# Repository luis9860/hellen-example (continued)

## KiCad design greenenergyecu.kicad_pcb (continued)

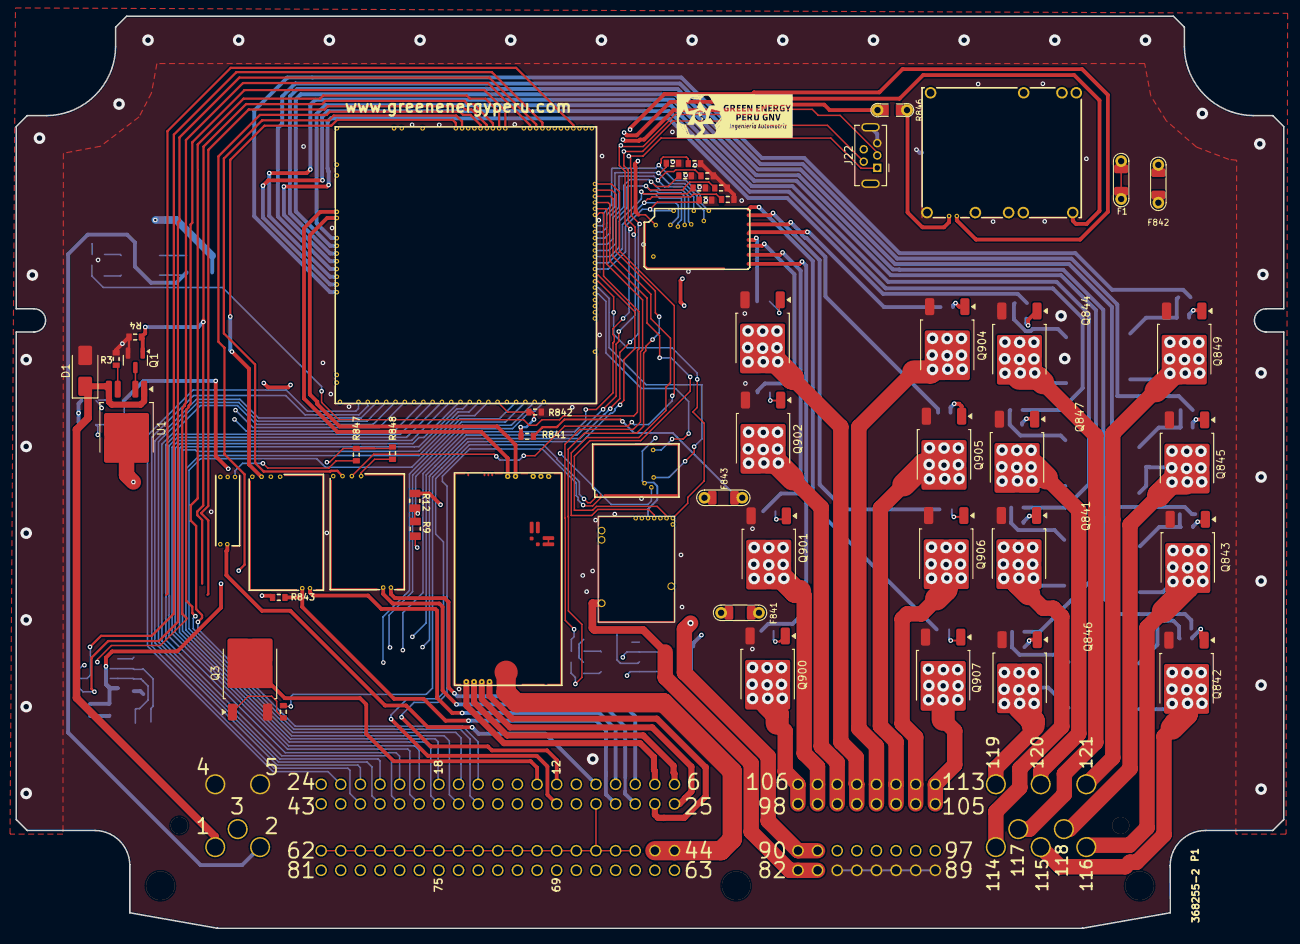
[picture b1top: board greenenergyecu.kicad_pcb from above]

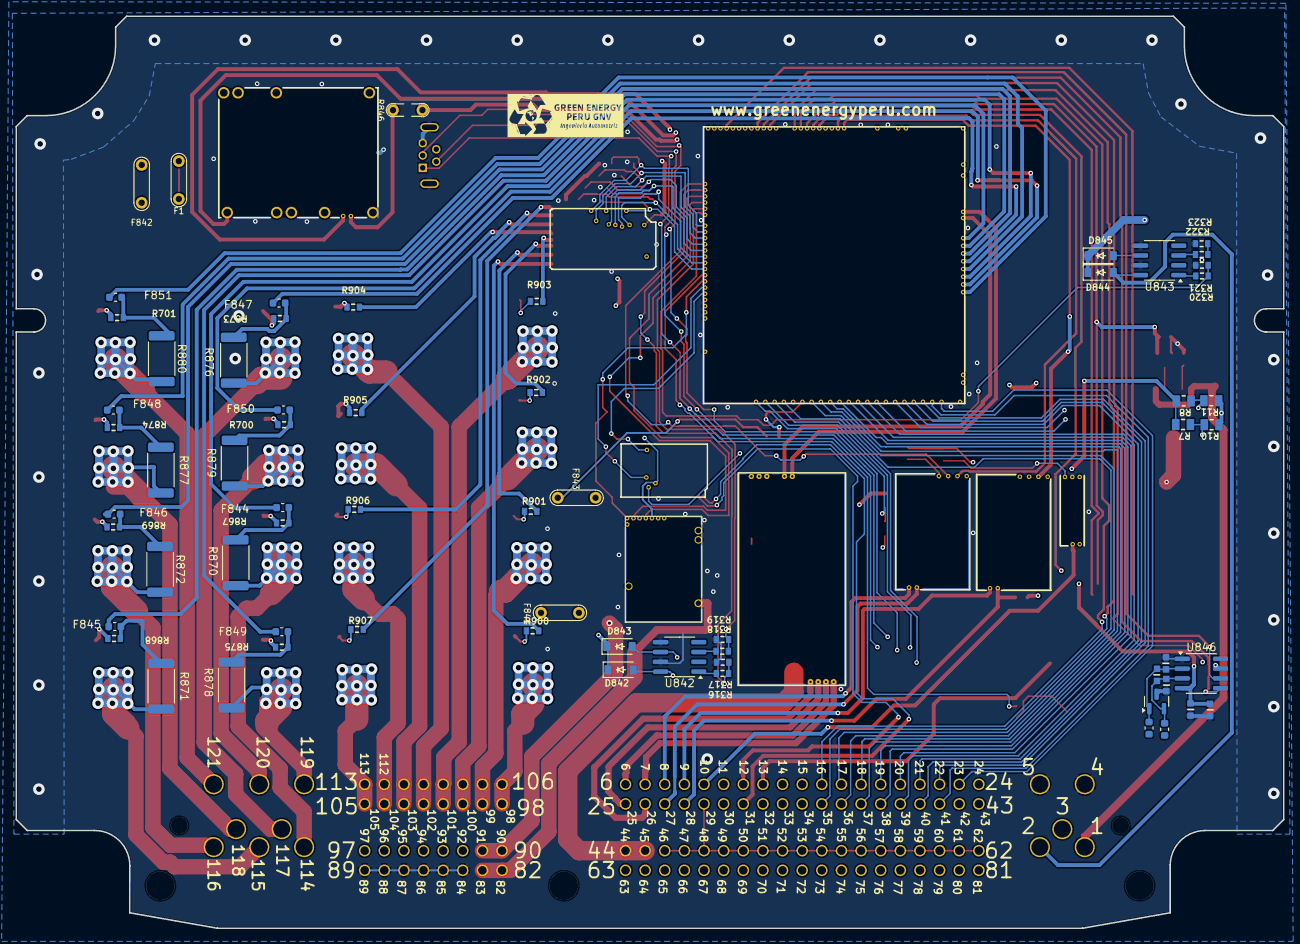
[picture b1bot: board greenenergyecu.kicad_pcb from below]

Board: 4 copper layers, 164.0 x 118.0 mm, 113 parts (59 on the bottom side), 159 nets.

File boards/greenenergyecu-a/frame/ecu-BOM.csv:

Comment,Designator,Footprint,LCSC Part #
"100n","C4","C0603","C14663"
"1u","C5","C0603","C15849"
"10n","C843","C0603","C57112"
"10n","C844","C0603","C57112"
"100n","C845","C0603","C14663"
"SS34","D1","D_SMA","C5119706"
"B5819W","D842","SOD-123","C8598"
"B5819W","D843","SOD-123","C8598"
"B5819W","D844","SOD-123","C8598"
"B5819W","D845","SOD-123","C8598"
"NUP2105L","D846","SOT-23","C284104"
"12H1500D","F1","PAD-1206-PAD","C182446"
"12H1500D","F841","PAD-1206-PAD","C182446"
"12H1500D","F842","PAD-1206-PAD","C182446"
"12H1500D","F843","PAD-1206-PAD","C182446"
"50mA","F844","Fuse_0603_1608Metric","C369141"
"50mA","F845","Fuse_0603_1608Metric","C369141"
"50mA","F846","Fuse_0603_1608Metric","C369141"
"50mA","F847","Fuse_0603_1608Metric","C369141"
"50mA","F848","Fuse_0603_1608Metric","C369141"
"50mA","F849","Fuse_0603_1608Metric","C369141"
"50mA","F850","Fuse_0603_1608Metric","C369141"
"50mA","F851","Fuse_0603_1608Metric","C369141"
"USB_B_Mini","J22","USB-MINI-B-VERTICAL","C2682228"
"470R@100MHz","L841","L_0603_1608Metric","C97853"
"470R@100MHz","L842","L_0603_1608Metric","C97853"
"Module:power_12and5V/0.3","M1","power_12and5V",""
"Module:knock/0.2","M2","knock",""
"Module:vr-discrete/0.5","M3","vr-discrete",""
"Module:vr-max9924/0.1","M4","vr-max9924",""
"Module:wbo/0.5","M5","wbo",""
"Module:mega-mcu100/0.3","M6","mega-mcu100",""
"Module:can/0.1","M7","can",""
"Module:motor-driver/0.1","M8","motor-driver",""
"Module:ign8/0.2","M9","ign8",""
"368255-2","P1","368255-2","C392284"
"AO3400A","Q1","SOT-23","C20917"
"ISL9V3040D3ST","Q3","DPAK","C903784"
"ISL9V3040D3ST","Q841","DPAK","C462128"
"ISL9V3040D3ST","Q842","MODIGBT","C462128"
"ISL9V3040D3ST","Q843","MODIGBT","C462128"
"ISL9V3040D3ST","Q844","DPAK","C462128"
"ISL9V3040D3ST","Q845","MODIGBT","C462128"
"ISL9V3040D3ST","Q846","DPAK","C462128"
"ISL9V3040D3ST","Q847","DPAK","C462128"
"ISL9V3040D3ST","Q849","MODIGBT","C462128"
"ISL9V3040D3ST","Q900","DPAK","C5350881"
"ISL9V3040D3ST","Q901","abel-252-2","C5350881"
"ISL9V3040D3ST","Q902","DPAK","C5350881"
"ISL9V3040D3ST","Q903","DPAK","C5350881"
"ISL9V3040D3ST","Q904","DPAK","C5350881"
"ISL9V3040D3ST","Q905","DPAK","C5350881"
"ISL9V3040D3ST","Q906","DPAK","C5350881"
"ISL9V3040D3ST","Q907","DPAK","C5350881"
"22","R1","R0603","C23345"
"1k","R3","R0603","C21190"
"4.7k","R4","R0603","C23162"
"DNP","R7","R0805",""
"DNP","R8","R0805",""
"DNP","R9","R0805",""
"10k","R10","R0805","C17414"
"10k","R11","R0805","C17414"
"10k","R12","R0805","C17414"
"10k","R305","R0603","C17414"
"10k","R307","R0603","C17414"
"10k","R309","R0603","C17414"
"10k","R311","R0603","C17414"
"10k","R313","R0603","C17414"
"10k","R315","R0603","C17414"
"4.7k","R316","R0603","C23162"
"4.7k","R317","R0603","C23162"
"4.7k","R318","R0603","C23162"
"4.7k","R319","R0603","C23162"
"4.7k","R320","R0603","C23162"
"4.7k","R321","R0603","C23162"
"4.7k","R322","R0603","C23162"
"4.7k","R323","R0603","C23162"
"10k","R325","R0603","C17414"
"10k","R327","R0603","C17414"
"22","R700","R0603","C23345"
"22","R701","R0603","C23345"
"33k","R841","R0603","C4216"
"6.8k","R842","R0603","C23212"
"4.7k","R843","R0603",""
"Jumper-Pad-Pad","R846","PAD-0805-PAD","C17477"
"0","R847","R0603","C21189"
"0","R848","R0603",""
"22","R867","R0603","C23345"
"22","R868","R0603","C23345"
"22","R869","R0603","C23345"
"0","R870","R2512",""
"0","R871","R2512",""
"0","R872","R2512",""
"22","R873","R0603","C23345"
"22","R874","R0603","C23345"
"22","R875","R0603","C23345"
"0","R876","R2512",""
"0","R877","R2512",""
"0","R878","R2512",""
"0","R879","R2512",""
"0","R880","R2512",""
"22","R900","R0603","C23345"
"22","R901","R0603","C23345"
"22","R902","R0603","C23345"
"22","R903","R0603","C23345"
"22","R904","R0603","C23345"
"22","R905","R0603","C23345"
"22","R906","R0603","C23345"
"22","R907","R0603","C23345"
"BTS6143D","U1","TO-252-4","C95232"
"VNLD5160TR-E","U842","SO8","C377942"
"VNLD5160TR-E","U843","SO8","C377942"
"MAX31855KASA","U846","SO8","C52028"

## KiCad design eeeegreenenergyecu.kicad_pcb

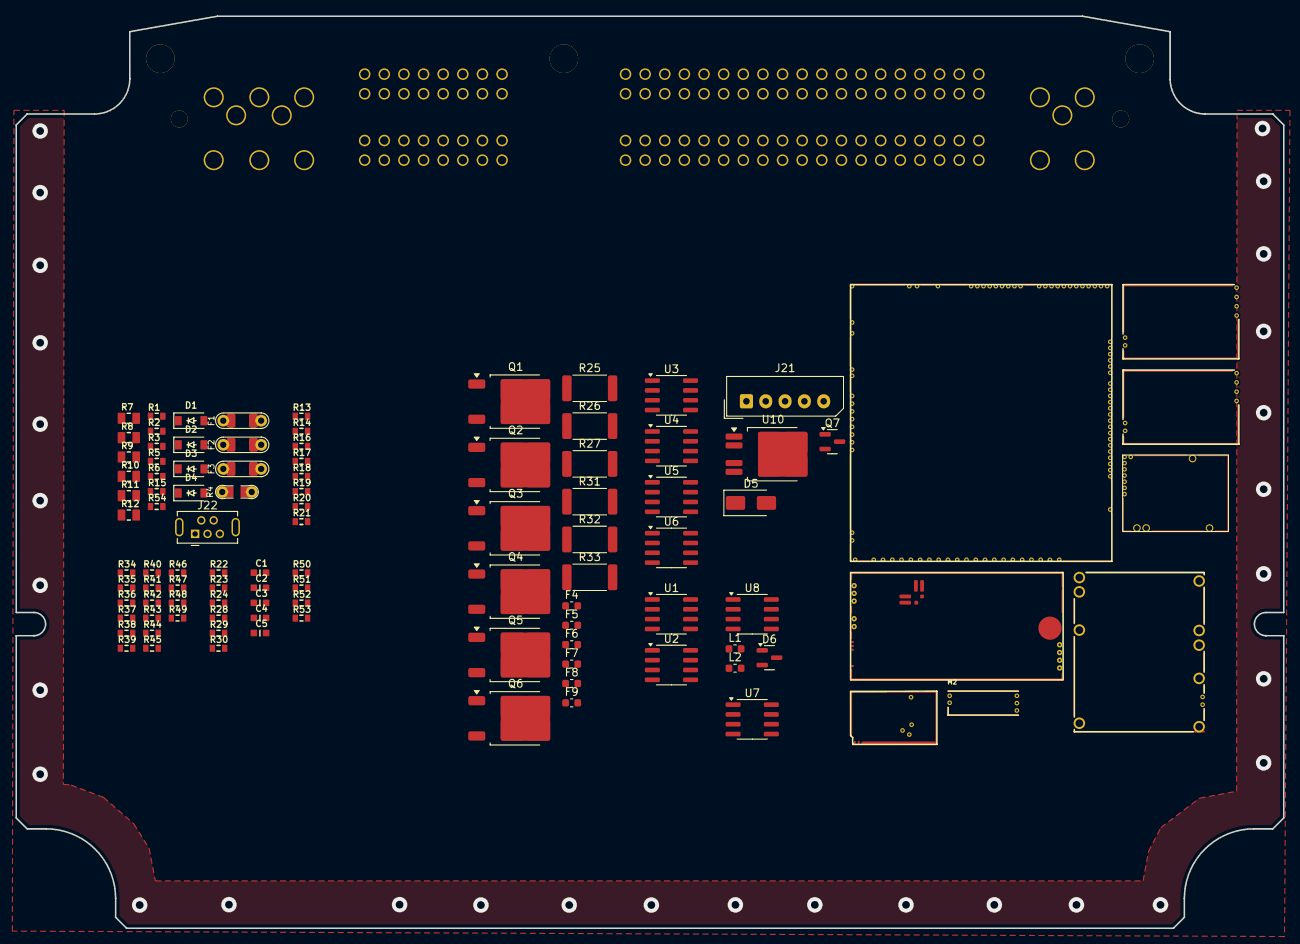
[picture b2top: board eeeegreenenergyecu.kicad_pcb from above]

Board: 4 copper layers, 164.0 x 118.0 mm, 103 parts (0 on the bottom side), 142 nets, no tracks yet.

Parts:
C1, C3: 10n; C0603
C2, C4: 100n; C0603
C5: 1u; C0603
D1, D2, D3, D4: B5819W; SOD-123
D5: SS34; D_SMA
D6: NUP2105L; SOT-23
F1, F2, F3: 12H1500D; PAD-1206-PAD
F4, F5, F6, F7, F8, F9: 50mA; Fuse_0603_1608Metric
J21: Conn_01x05_Male; Molex_SPOX_5267-05A_1x05_P2.50mm_Vertical
J22: USB_B_Mini; USB-MINI-B-VERTICAL
L1, L2: 470R@100MHz; L_0603_1608Metric
M1: Module-power_12and5V-0.3; power_12and5V
M2: Module-knock-0.2; knock
M3: Module-vr-discrete-0.5; vr-discrete
M4: Module-vr-max9924-0.1; vr-max9924
M5: Module-wbo-0.5; wbo
M6: Module:mega-mcu100/0.3; mega-mcu100
M7: Module-can-0.1; can
M8: Module-motor-driver-0.1; motor-driver
P1: 368255-2
Q1, Q2, Q3, Q4, Q5, Q6: ISL9V3040D3ST; TO-252-2
Q7: AO3400A; SOT-23
R1, R13, R14, R15, R16, R17, R18, R19, R20, R21, R34, R35, R36, R37, R38, R39, R40, R41, R42, R43, R44, R45, R46, R47, R48, R49, R50, R51, R52, R53: 4.7k; R0603
R2: 33k; R0603
R3: 6.8k; R0603
R4: Jumper-Pad-Pad; PAD-0805-PAD
R5, R6: 0; R0603
R7, R8, R9: DNP; R0805
R10, R11, R12: 10k; R0805
R22, R23, R24, R28, R29, R30: 22; R0603
R25, R26, R27, R31, R32, R33: 0; R_2512_6332Metric
R54: 1k; R0603
U1, U2, U3, U4, U5, U6, U7: VNLD5160TR-E; SOIC-8_3.9x4.9mm_P1.27mm
U8: MAX31855KASA; SOIC-8_3.9x4.9mm_P1.27mm
U10: BTS6143D; TO-252-4

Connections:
+3.3V: M6.N21 (V33), M8.W5 (3V3_IN)
+3.3VA: C4.2, C5.2, M6.N15 (V33_SWITCHABLE), M7.V2 (CAN_VIO), U8.4 (V_CC)
+5V: M1.E4 (V5), M6.N22 (VCC)
+5VA: M2.E1 (V5A), M3.E4 (V5_IN), M4.E4 (V5_IN), M5.W1 (V5_IN), M6.E1 (V5A_SWITCHABLE), M6.W2 (V5A_SWITCHABLE), M7.V1 (V5), R7.2, R8.2, R9.2
/ADC3: M6.S15 (IN_KNOCK_(PA2)), R5.2, R6.2
/DC1_DIR: M6.E21 (OUT_PWM4_(PC8)), M8.W4 (DIR)
/DC1_PWM: M6.E20 (OUT_PWM3_(PC7)), M8.W2 (PWM)
/EGT/SPI_CS: M6.N9 (SPI3_CS_(PA15)), U8.6 (~CS)
/IGN1: F4.2, M6.W10 (IGN1_(PC13))
/IGN2: F5.2, M6.W9 (IGN2_(PE5))
/IGN3: F6.2, M6.W8 (IGN3_(PE4))
/IGN4: F7.2, M6.W7 (IGN4_(PE3))
/IGN5: F8.2, M6.W6 (IGN5_(PE2))
/IGN6: F9.2, M6.W5 (IGN6_(PB8))
/INJ1: M6.E17 (OUT_INJ1_(PD3)), R38.1, R39.1
/INJ2: M6.E16 (OUT_INJ2_(PA9)), R40.1, R41.1
/INJ3: M6.E15 (OUT_INJ3_(PD11)), R42.1, R43.1
/INJ4: M6.E14 (OUT_INJ4_(PD10)), R44.1, R45.1
/INJ5: M6.E13 (OUT_INJ5_(PD2)), R46.1, R47.1
/INJ6: M6.E12 (OUT_INJ6_(PA8)), R48.1, R49.1
/IN_KNOCK: M2.E3 (OUT_KNOCK), R5.1
/IN_VIGN: F1.2, M1.V2 (IN_VIGN)
/IN_VMAIN: M6.S6 (IN_AUX4_(PC5)), R2.1, R3.2
/LS1: M6.E11 (OUT_INJ7_(PD15)), R13.1, R16.1
/LS2: M6.E10 (OUT_INJ8_(PD12)), R14.1, R17.1
/LS3: M6.E18 (OUT_PWM1_(PD13)), R18.1, R20.1
/LS4: M6.E19 (OUT_PWM2_(PC6)), R19.1, R21.1
/LS_HOT1: M6.W4 (IGN7_(PB9)), R52.1, R53.1
/LS_HOT2: M6.W3 (IGN8_(PE6)), R50.1, R51.1
/MISO3: M6.N11 (SPI3_MISO_(PC11)), U8.7 (SO)
/PG_5VP: M6.N12 (SPI3_MOSI_(PC12)), R4.2
/PWR_EN: M1.E5 (EN_5VP), M6.N20 (OUT_PWR_EN_(PE10))
/SCK3: M6.N10 (SPI3_SCK_(PC10)), U8.5 (SCK)
/USB+: J21.3, J22.3 (D+), M6.N3 (USBP_(PA12))
/USB-: J21.2, J22.2 (D-), M6.N2 (USBM_(PA11))
/VBAT: M1.E1 (VBAT), M6.N17 (VBAT)
/VBUS: J21.1, J22.1 (VBUS), M6.N1 (VBUS)
/VIGN: M1.E3 (VIGN), M6.E5 (IN_VIGN_(PA5))
/VREF1: M2.W2 (VREF), M6.S22 (VREF1)
/VR_DISCRETE: M3.E3 (OUT), M6.N18 (UART8_RX_(PE0))
/VR_DISCRETE_A: M3.E2 (OUT_A), R6.1
/VR_DISCRETE_THR: M3.E1 (Thresh_IN), M6.E23 (OUT_PWM6_(PD14))
/VR_MAX9924: M4.E3 (OUT), M6.N19 (UART8_TX_(PE1))
DC1_DIS_W1: M6.E8 (SPI2_MISO_(PB14)), M8.W1 (DIS)
E6INJ7CANRX: M6.E6 (SPI2_CS_/_CAN2_RX_(PB12)), M7.V6 (CAN_RX), R34.1, R37.1
E7INJ8CANTX: M6.E7 (SPI2_SCK_/_CAN2_TX_(PB13)), M7.V5 (CAN_TX), R35.1, R36.1
unnamed: F3.2, M8.N2 (12V_IN), M8.S1 (12V_IN)
unnamed: F4.1, R22.2, R25.1
unnamed: F5.1, R23.2, R26.1
unnamed: F6.1, R24.2, R27.1
unnamed: F7.1, R28.2, R31.1
unnamed: F8.1, R29.2, R32.1
unnamed: F9.1, R30.2, R33.1
unnamed: M1.E6 (PG_5VP), R4.1
unnamed: M5.J1 (SEL1), M5.J_GND1 (PULL_DOWN1)
unnamed: M6.N14a (LED_GREEN), Q7.1 (G), R15.1
unnamed: Q1.1 (G), R22.1
unnamed: Q2.1 (G), R23.1
unnamed: Q3.1 (G), R24.1
unnamed: Q4.1 (G), R28.1
unnamed: Q5.1 (G), R29.1
unnamed: Q6.1 (G), R30.1
unnamed: Q7.3 (D), U10.2 (IN)
unnamed: R13.2, U1.1 (IN1)
unnamed: R14.2, U1.3 (IN2)
unnamed: R18.2, U2.1 (IN1)
unnamed: R19.2, U2.3 (IN2)
unnamed: R34.2, U3.1 (IN1)
unnamed: R36.2, U3.3 (IN2)
unnamed: R42.2, U4.1 (IN1)
unnamed: R45.2, U4.3 (IN2)
unnamed: R46.2, U5.1 (IN1)
unnamed: R48.2, U5.3 (IN2)
unnamed: R38.2, U6.1 (IN1)
unnamed: R41.2, U6.3 (IN2)
unnamed: R50.2, U7.1 (IN1)
unnamed: R52.2, U7.3 (IN2)
unnamed: C2.2, C3.2, D6.2 (K), L1.2, U8.3 (T+)
unnamed: C1.2, C2.1, D6.1 (K), L2.2, U8.2 (T-)
unnamed: R54.1, U10.4 (IS)
PIN1: M8.S3 (OUT+), P1.1
PIN2: M8.S2 (OUT-), P1.2
PIN6: M6.N14 (UART2_RX_(PD6)), P1.6
PIN7: M6.N13 (UART2_TX_(PD5)), P1.7
PIN8: P1.8, Q6.2 (C), R33.2
PIN9: P1.9, Q4.2 (C), R31.2
PIN10: P1.10, Q3.2 (C), R27.2
PIN11: P1.11, Q5.2 (C), R32.2
PIN12: P1.12, Q2.2 (C), R26.2
PIN13: P1.13, Q1.2 (C), R25.2
PIN14: D1.2 (A), P1.14, U1.8 (D1)
PIN15: D2.2 (A), P1.15, U1.6 (D2)
PIN16: D3.2 (A), P1.16, U2.8 (D1)
PIN17: M3.W2 (VR+), P1.17
PIN18: M3.W1 (VR-), P1.18
PIN19: M4.W2 (VR+), P1.19
PIN20: M4.W1 (VR-), P1.20, R1.2
PIN21: L1.1, P1.21
PIN22: L2.1, P1.22
PIN34: M6.S2 (IN_D3_(PE14)), P1.34
PIN35: M6.S3 (IN_D2_(PE13)), P1.35
PIN36: M6.S4 (IN_D1_(PE12)), P1.36
PIN37: M6.S13 (IN_MAP1_(PC0)), P1.37
PIN38: M6.S18 (IN_TPS_(PA4)), P1.38
PIN39: M6.S9 (IN_AUX1_(PB0)), P1.39
PIN40: M6.S11 (IN_O2S_/_CAN_WAKEUP_(PA0)), P1.40
PIN41: M6.S10 (IN_O2S2_(PA1)), P1.41
PIN42: M6.S17 (IN_VSS_(PE11)), P1.42
PIN43: D5.1 (K), P1.43, U10.1 (OUT), U10.5 (OUT)
PIN44: P1.44, U6.8 (D1)
PIN45: P1.45, U6.6 (D2)
PIN46: P1.46, U4.8 (D1)
PIN47: P1.47, U4.6 (D2)
PIN48: P1.48, U5.8 (D1)
PIN49: P1.49, U5.6 (D2)
PIN50: P1.50, U3.8 (D1)
PIN51: P1.51, U3.6 (D2)
PIN63: M6.S20 (IN_IAT_(PC3)), P1.63
PIN65: M6.S21 (IN_CLT_(PC2)), P1.65
PIN81: M2.W1 (IN_KNOCK), P1.81
PIN82: M5.W4 (CANH), M6.W11 (CANH), P1.82
PIN83: M5.W3 (CANL), M6.W12 (CANL), P1.83
PIN84: M6.S14 (IN_CRANK_(PB1)), P1.84, R7.1, R10.2
PIN85: M6.S16 (IN_CAM_(PA6)), P1.85, R8.1, R11.2
PIN86: P1.86, U7.6 (D2)
PIN87: P1.87, U7.8 (D1)
PIN88: D4.2 (A), P1.88, U2.6 (D2)
PIN89: M6.S1 (IN_D4_(PE15)), P1.89, R9.1, R12.2
PIN90: M6.S19 (IN_PPS_(PA3)), P1.90
PIN91: M6.S8 (IN_AUX2_(PC4/PE9)), P1.91
PIN102: M5.E4 (LSU_Rtrim), P1.102
PIN103: M5.E3 (LSU_Ip), P1.103
PIN104: M5.E2 (LSU_Vm), P1.104
PIN105: M5.E1 (LSU_Un), P1.105
PIN106: M1.V4 (5VP), P1.71, P1.72, P1.73, P1.74, P1.75, P1.76, P1.77, P1.78, P1.79, P1.80, P1.106, P1.107, R1.1
PIN108: F1.1, P1.108
PIN113: M6.W1 (GNDA), P1.52, P1.53, P1.54, P1.55, P1.56, P1.57, P1.58, P1.59, P1.60, P1.61, P1.62, P1.64, P1.66, P1.68, P1.98, P1.99, P1.113, R10.1, R11.1, R12.1
PIN114: C1.1, C3.1, C4.1, C5.1, D5.2 (A), D6.3 (A), J21.4, J21.5, J22.5 (GND), J22.6 (Shield), M1.S1 (GND), M2.E2 (GND), M3.G (GND), M4.G (GND), M5.E6 (LSU_H-), M5.G (GND), M6.G (GND), M7.E1 (GND), M8.G (GND), P1.3, P1.114, P1.115, Q1.3 (E), Q2.3 (E), Q3.3 (E), Q4.3 (E), Q5.3 (E), Q6.3 (E), Q7.2 (S), R3.1, R15.2, R16.2, R17.2, R20.2, R21.2, R35.2, R37.2, R39.2, R40.2, R43.2, R44.2, R47.2, R49.2, R51.2, R53.2, R54.2, U1.5 (S2), U1.7 (S1), U2.5 (S2), U2.7 (S1), U3.5 (S2), U3.7 (S1), U4.5 (S2), U4.7 (S1), U5.5 (S2), U5.7 (S1), U6.5 (S2), U6.7 (S1), U7.5 (S2), U7.7 (S1), U8.1 (GND)
PIN116: M1.V1 (V12_PERM), P1.116
PIN117: D1.1 (K), D2.1 (K), D3.1 (K), D4.1 (K), F2.2, M1.V3 (V12_RAW), P1.117
PIN119: M5.E5 (LSU_H+), P1.119
PIN120: F2.1, F3.1, P1.23, P1.24, P1.120, R2.2, U10.3 (Vbb)

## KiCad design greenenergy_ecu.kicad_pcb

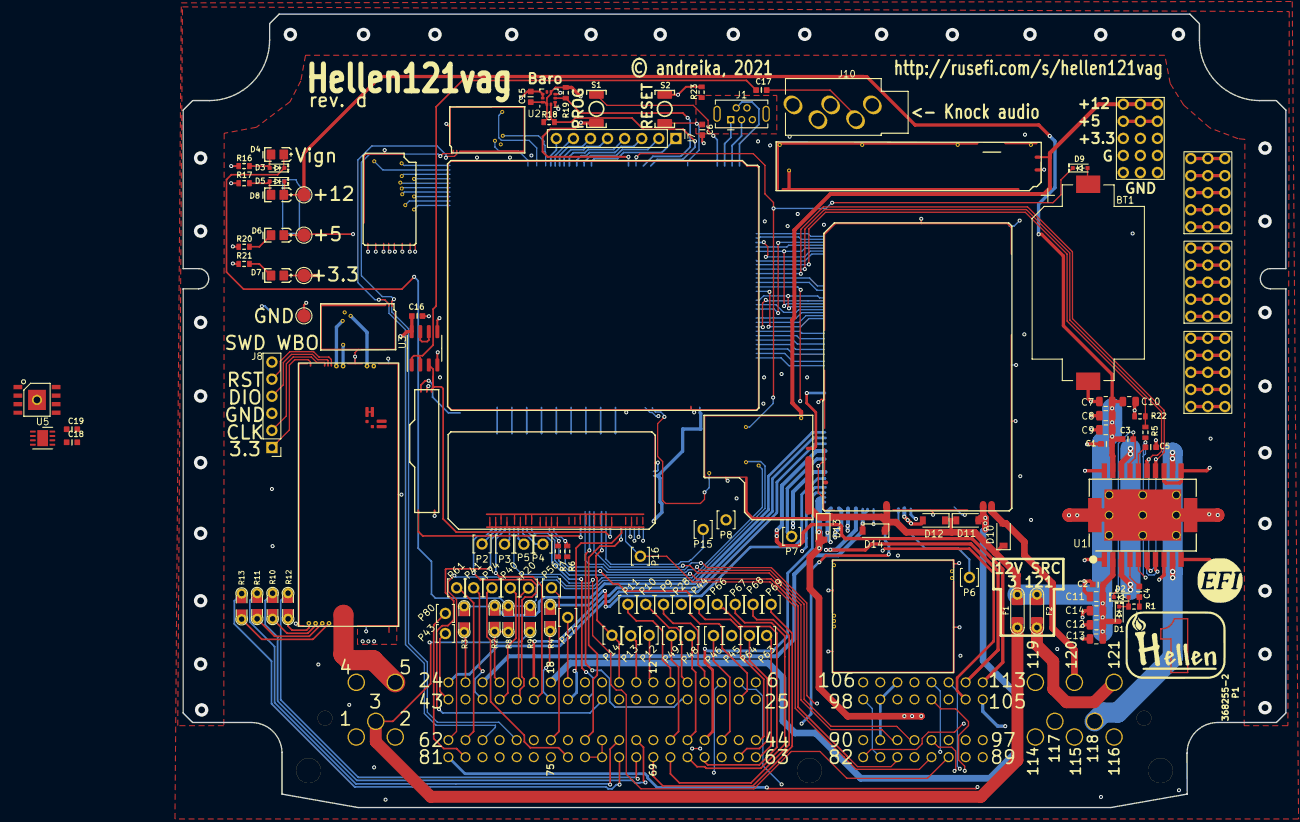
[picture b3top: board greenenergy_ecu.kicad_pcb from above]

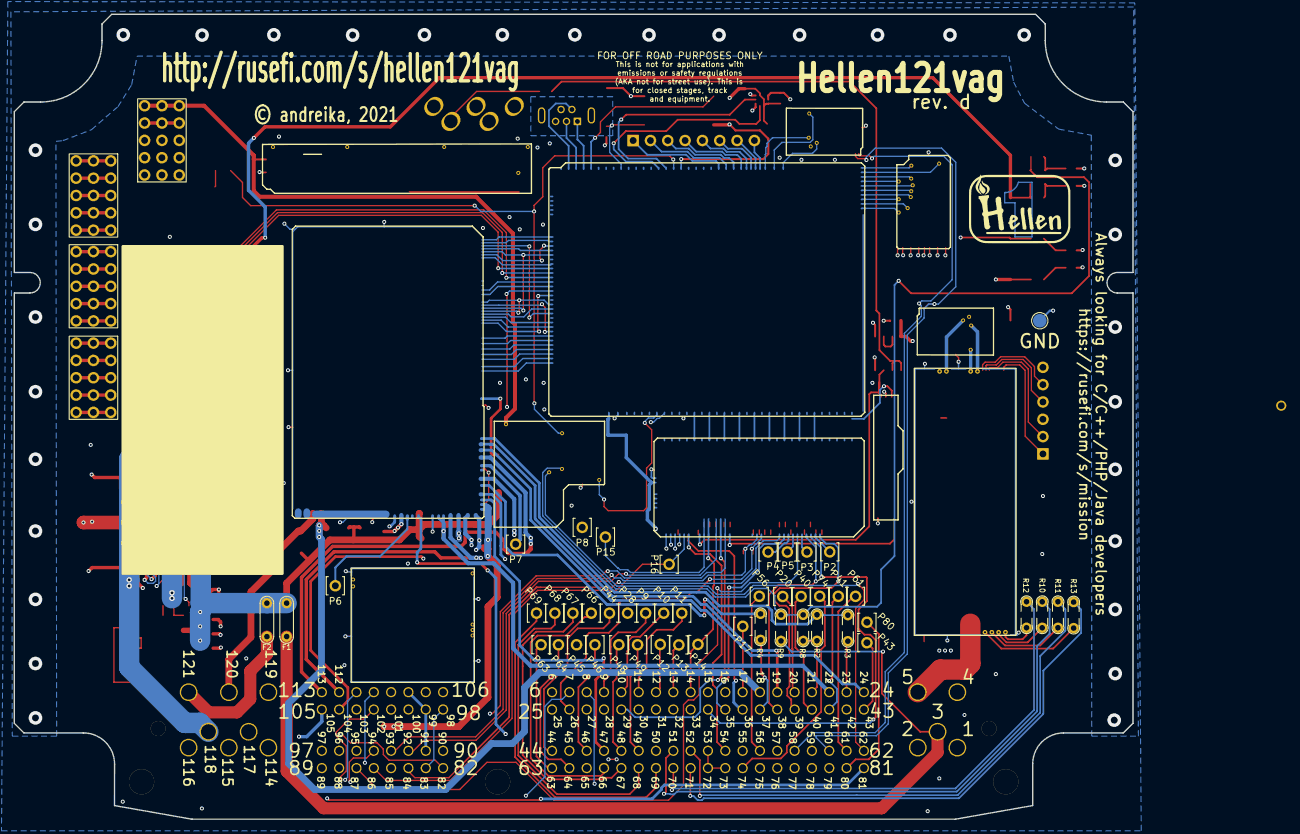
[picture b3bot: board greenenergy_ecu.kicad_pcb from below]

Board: 4 copper layers, 164.0 x 118.0 mm, 128 parts (2 on the bottom side), 231 nets.

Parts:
BT1: BATTERY_CR2032; BatteryHolder_Keystone_1060_1x2032
C1, C2, C6, C15, C16: 100n; C0603
C3: 220n; C0603
C4: 10n; C0603
C5: 5.6n; C0603
C7, C8, C9, C10, C11, C12, C13, C14: 10u; C_0805_2012Metric
C17: 10u; C0603
C18, C19: 1u; C0603
D1, D2, D3, D5, D9: 1N4148WS; SOD-323
D4, D6, D7, D8: LED-GREEN-0805; LED-0805
D10, D11, D12, D13, D14: B5819W; D_SOD-123
F1, F2: Fuse-Pad-Pad; PAD-1206-PAD
G1, G2, G3, G5: PROTO_AREA
G4: DISCLAIMER; Off_Road_Disclaimer
G6, G7: LOGO
J1: USB_B_Mini; USB-MINI-B-VERTICAL
J2, J3, J4, J5, J6: Conn_01x01; TestPoint_Pad_D2.0mm
J7: Conn_01x08; PinHeader_1x08_P2.54mm_Vertical
J8: Conn_01x06; PinHeader_1x06_P2.54mm_Vertical
J10: AudioJack_THR; Jack_3.5mm_PJ-3250-5A
M1, M10: Module-can-0.1; can
M2: Module-power5-0.2; power5
M3: Module-mcu-0.7; mcu
M4: Module-input-0.1; input
M5: Module-knock-0.1; knock
M6: Module-output-0.3; output
M7: Module-ign8-0.2; ign8
M8: Module-power12-0.2; power12
M9: Module-wbo-0.3; wbo
M11: Module-vr-discrete-0.1; vr-discrete
P1: 368255-2
P2, P3, P4, P5, P6, P7, P8, P9, P10, P11, P12, P13, P14, P15, P16, P17, P20, P28, P40, P41, P43, P44, P45, P46, P48, P49, P56, P61, P63, P64, P66, P67, P68, P69, P74, P80: Pad; PAD-TH
R1: 100; R0603
R2, R3, R4, R8, R9, R10, R11, R12, R13: Jumper-Pad-Pad; PAD-0805-PAD
R5: 100k; R0603
R6, R7: 2.7k; R0603
R16, R17: 5.1k; R0603
R18, R19: 4.7k; R0603
R20: 1.6k; R0603
R21: 750; R0603
R22: 10k; R0603
R23: 0; R0603
S1, S2: Button_SPST; SMD-2_2.9x3.9x1.7
U1: L6205PD; SO20POWER
U2: LPS25HB; ST_HLGA-10_2.5x2.5mm_P0.6mm_LayoutBorder3x2y
U3: MCP6002-xSN; SOIC-8_3.9x4.9mm_P1.27mm
U4: TLS115_SOIC; PG-DSO-8-43_VIA
U5: TLS115_SON; HVSON-8-1EP_3x3mm_P0.65mm_EP1.6x2.4mm

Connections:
+3V3: C15.2, D7.1 (A), G3.3, G3.8, G3.13, J4.1, M3.N16 (V33), R18.1, R19.1, S1.2, U2.1 (VDDio), U2.6 (~CS), U2.10 (VDD)
+5V: C16.2, D6.1 (A), G3.2, G3.7, G3.12, J3.1, M1.V1 (V5), M2.V2 (V5), M3.S1 (V5), M4.E2 (V5), M6.W14 (V5), M8.E1 (V5), M9.W1 (V5_IN), M10.V1 (V5), M11.E4 (V5_IN), U3.8 (V+), U4.5 (ADJ), U5.5 (ADJ)
+5VA: M3.S33 (V5A), M4.E5 (V5A), M4.J1 (PULL_V5A), M4.J5 (PULL_PPS), M4.J7 (PULL_AUX4), M4.J9 (PULL_AUX2), M4.J10 (PULL_AUX1), M4.J17 (PULL_CAM), M4.J18 (PULL_VSS), M4.J19 (PULL_TPS), M4.J20 (PULL_O2S), M4.J21 (PULL_CRANK), M4.N1 (V5A), M5.E1 (V5A), R6.2, R7.2
+5VP: C19.2, P1.53, P1.72, P1.73, P1.83, P1.98, U4.1 (OUT), U5.1 (OUT)
+12V: G3.1, G3.6, G3.11, M2.V1 (V12), M8.V1 (V12)
+12V_PROT: C18.2, M6.W5 (V12P), U4.7 (EN), U4.8 (IN), U5.7 (EN), U5.8 (IN)
+12V_RAW: C1.2, C2.2, C3.2, C7.2, C8.2, C9.2, C10.2, C11.2, C12.2, C13.2, C14.2, D1.2 (A), D5.1 (K), D8.1 (A), D10.1 (K), D11.1 (K), D12.1 (K), D13.1 (K), D14.1 (K), F1.2, F2.2, J2.1, M6.S11 (V12_RAW), M8.E2 (V12_RAW), U1.2 (VSA), U1.19 (VSB)
/+ETB: M3.E14 (OUT_PWM2), U1.7 (IN2A), U1.15 (IN2B)
/+ETB_OUT: P1.117, U1.3 (OUT2A), U1.18 (OUT2B)
/-ETB: M3.E15 (OUT_PWM3), U1.6 (IN1A), U1.14 (IN1B)
/-ETB_OUT: P1.118, U1.9 (OUT1A), U1.12 (OUT1B)
/A1: M3.S30 (IN_O2S2), M4.N4 (O2S2)
/A2: M3.S22 (IN_MAP3), M4.N12 (MAP3)
/A3: M3.S26 (IN_AUX3), M4.N8 (AUX3)
/A4: M3.S23 (IN_DIG3), M4.N11 (RES3)
/AFR: M3.S16 (IN_O2S), M4.N18 (O2S)
/BOOT0: M3.N28 (BOOT0), S1.1
/CAM1: M3.S15 (IN_AN_DIG2), M4.N19 (CAM)
/CAM2: M3.S27 (IN_AUX4), M4.N7 (AUX4)
/CAN+: M1.S2 (CANH), M10.S2 (CANH), P1.60
/CAN-: M1.S1 (CANL), M10.S1 (CANL), P1.58
/CAN_RX: M1.V6 (CAN_RX), M3.N2 (CAN_RX)
/CAN_TX: M1.V5 (CAN_TX), M3.N3 (CAN_TX)
/CAN_VIO: M1.V2 (CAN_VIO), M3.N1 (CAN_VIO)
/CHECK_ENGINE: M3.E22 (OUT_IO8), M6.W25 (LOW6_DIODE)
/CLT: M3.S18 (IN_CLT), M4.N16 (CLT)
/CRANK: M3.S13 (IN_AN_DIG1), M4.N21 (CRANK)
/D1: M3.S3 (IN_DIG8), M4.N26 (SENS1)
/D2: M3.S4 (IN_DIG9), M4.N25 (SENS2)
/D3: M3.S5 (IN_DIG10), M4.N24 (SENS3)
/D4: M3.S6 (IN_DIG11), M4.N23 (SENS4)
/ETB_EN: M3.E13 (OUT_IO12), R5.1, R22.1
/FUEL_CONSUM: M3.E19 (OUT_PWM7), M6.W22 (PP2)
/FUEL_PUMP_RELAY: M3.E8 (OUT_IO1), M6.W35 (LOW11)
/IAT: M3.S19 (IN_IAT), M4.N15 (IAT)
/IDLE: M3.E23 (OUT_IO4), M6.W38 (LOW3_DUAL)
/IGN1: M3.W1 (OUT_IGN1), M7.V8 (IGN1)
/IGN2: M3.W2 (OUT_IGN2), M7.V7 (IGN2)
/IGN3: M3.W3 (OUT_IGN3), M7.V6 (IGN3)
/IGN4: M3.W4 (OUT_IGN4), M7.V5 (IGN4)
/IGN5: M3.W5 (OUT_IGN5), M7.V4 (IGN5)
/IGN6: M3.W6 (OUT_IGN6), M7.V3 (IGN6)
/IGN7: M3.W7 (OUT_IGN7), M7.V2 (IGN7)
/IGN8: M3.W8 (OUT_IGN8), M7.V1 (IGN8)
/IGN_V5: M3.W9 (IGN_V5), M7.V9 (VCC)
/IGN_V33: M3.W10 (IGN_V33), M7.V10 (V33)
/INJ1: M3.E25 (OUT_INJ1), M6.W24 (INJ1)
/INJ2: M3.E26 (OUT_INJ2), M6.W23 (INJ2)
/INJ3: M3.E29 (OUT_INJ3), M6.W20 (INJ3)
/INJ4: M3.E30 (OUT_INJ4), M6.W19 (INJ4)
/INJ5: M3.E31 (OUT_INJ5), M6.W18 (INJ5)
/INJ6: M3.E32 (OUT_INJ6), M6.W17 (INJ6)
/INJ7: M3.E33 (OUT_INJ7), M6.W16 (INJ7)
/INJ8: M3.E34 (OUT_INJ8), M6.W15 (INJ8)
/IN_A1: M4.S25 (IN_O2S2), P2.1
/IN_A2: M4.S19 (IN_MAP3), P4.1
/IN_A3: M4.S20 (IN_AUX3), P5.1
/IN_A4: M4.S22 (IN_RES3), P3.1
/IN_AFR: M4.S9 (IN_O2S), P1.14, P14.1
/IN_CAM1: M4.S5 (IN_CAM), P1.86, P16.1
/IN_CAM2: M4.S21 (IN_AUX4), P1.87
/IN_CLT: M4.S15 (IN_CLT), P1.93, R6.1
/IN_CRANK: M4.S8 (IN_CRANK), M11.E3 (OUT), P15.1
/IN_CRANK+: M11.W2 (VR+), P1.82
/IN_CRANK-: M11.W1 (VR-), P1.90
/IN_D1: M4.S1 (IN_SENS1), P1.55
/IN_D2: M4.S2 (IN_SENS2), P1.57
/IN_D3: M4.S3 (IN_SENS3), P1.75
/IN_D4: M4.S4 (IN_SENS4), P1.76
/IN_IAT: M4.S16 (IN_IAT), P1.26, P1.85, R7.1
/IN_KNOCK1: M4.S7 (IN_KNOCK), M5.E3 (OUT_KNOCK), U3.3 (+)
/IN_KNOCK1_RAW: M5.W1 (IN_KNOCK), P1.106
/IN_MAF: M4.S11 (IN_MAP1), P1.29
/IN_MAP2: M4.S12 (IN_MAP2), P1.101
/IN_PPS1: M4.S24 (IN_PPS), P1.34
/IN_PPS2: M4.S18 (IN_AUX2), P1.35
/IN_RES1: M4.S23 (IN_RES1), P1.38
/IN_RES2: M4.S26 (IN_RES2), P1.39
/IN_TPS1: M4.S10 (IN_TPS), P1.92
/IN_TPS2: M4.S17 (IN_AUX1), P1.84
/IN_VIGN: D3.1 (K), D4.1 (A), M8.V3 (IN_VIGN), R8.1, R9.2
/IN_VSS: M4.S6 (IN_VSS), P1.54
/KNOCK1: M3.S12 (IN_KNOCK), M4.N22 (KNOCK)
/LSU_CALIBR_RES: M9.E4 (LSU_Rtrim), R13.2
/LSU_HEAT-: M9.E5 (LSU_H+), P1.5
/LSU_PUMP_I: M9.E3 (LSU_Ip), R11.2
/LSU_SENSOR_U: M9.E1 (LSU_Un), R12.2
/LSU_SENSOR_U/PUMP_I: M9.E2 (LSU_Vm), R10.2
/MAF: M3.S20 (IN_MAP1), M4.N14 (MAP1)
/MAIN_RELAY: M3.E6 (OUT_IO3), M6.W40 (LOW5_MAIN)
/MAP2: M3.S21 (IN_MAP2), M4.N13 (MAP2)
/NRESET: C6.2, M3.N24 (nReset), S2.1
/OUT1: M3.E7 (OUT_IO5), M6.W39 (LOW7_HIGH1)
/OUT2: M3.E9 (OUT_IO6), M6.W37 (LOW8_HIGH2)
/OUT3: M3.E28 (OUT_PWM8), M6.W21 (LOW1)
/OUT_CHECK_ENGINE: M6.W3 (OUT_LOW6_DIODE), P1.47
/OUT_FUEL_CONSUM: M6.S6 (OUT_PP2), P1.81
/OUT_FUEL_PUMP_RELAY: M6.S10 (OUT_LOW11), P1.65
/OUT_IDLE: D12.2 (A), M6.S7 (OUT_LOW3_DUAL), P1.105
/OUT_IGN1: M7.S8 (OUT_IGN1), P1.102
/OUT_IGN2: M7.S7 (OUT_IGN2), P1.7
/OUT_IGN3: M7.S6 (OUT_IGN3), P1.111
/OUT_IGN4: M7.S5 (OUT_IGN4), P1.94
/OUT_IGN5: M7.S4 (OUT_IGN5), P1.103
/OUT_IGN6: M7.S3 (OUT_IGN6), P1.110
/OUT_IGN7: M7.S2 (OUT_IGN7), P1.8
/OUT_IGN8: M7.S1 (OUT_IGN8), P1.95
/OUT_INJ1: M6.S18 (OUT_INJ1), P1.96
/OUT_INJ2: M6.S16 (OUT_INJ2), P1.89
/OUT_INJ3: M6.S17 (OUT_INJ3), P1.97
/OUT_INJ4: M6.W7 (OUT_INJ4), P1.88
/OUT_INJ5: M6.W10 (OUT_INJ5), P1.113
/OUT_INJ6: M6.S15 (OUT_INJ6), P1.112
/OUT_INJ7: M6.W12 (OUT_INJ7), P1.19
/OUT_INJ8: M6.W11 (OUT_INJ8), P1.24
/OUT_MAIN_RELAY: M6.W13 (OUT_LOW5_MAIN), R2.2, R3.1
/OUT_TACH: M6.W6 (OUT_PP1), R4.2
/OUT_VVT1_1: D14.2 (A), M6.S13 (OUT_LOW12), M6.S14 (OUT_LOW9), P1.22
/OUT_VVT1_2: D13.2 (A), M6.W1 (OUT_LOW2), M6.W2 (OUT_LOW10), P1.115
/OUT_VVT2_B1: D11.2 (A), M6.S5 (OUT_SOLENOID_B2), P1.18
/OUT_VVT2_B2: D10.2 (A), M6.S4 (OUT_SOLENOID_B1), P1.120
/OUT_WASTEGATE: M6.W4 (OUT_LOW4_DUAL), P1.104
/PPS1: M3.S29 (IN_PPS), M4.N5 (PPS)
/PPS2: M3.S25 (IN_AUX2), M4.N9 (AUX2)
/RES1: M3.S28 (IN_DIG1), M4.N6 (RES1)
/RES2: M3.S31 (IN_DIG2), M4.N3 (RES2)
/RX1: J7.7, M3.N5 (UART8_RX)
/RX2: J7.5, M3.N7 (UART2_RX)
/SPI3_CS: J7.4, M3.N8 (SPI3_CS)
/SPI3_MISO: J7.2, M3.N10 (SPI3_MISO)
/SPI3_MOSI: J7.1, M3.N11 (SPI3_MOSI)
/SPI3_SCK: J7.3, M3.N9 (SPI3_SCK)
/TACH: M3.E27 (OUT_PWM1), M6.W28 (PP1)
/THRESHOLD_VR: M3.E18 (OUT_PWM6), M11.E1 (Thresh_IN)
/TPS1: M3.S17 (IN_TPS), M4.N17 (TPS)
/TPS2: M3.S24 (IN_AUX1), M4.N10 (AUX1)
/TX1: J7.8, M3.N4 (UART8_TX)
/TX2: J7.6, M3.N6 (UART2_TX)
/USBM: J1.2 (D-), M3.N31 (USB1M)
/USBP: J1.3 (D+), M3.N30 (USB1P)
/V12_PERM: M8.V4 (V12_PERM), P1.62
/VBAT: D9.1 (K), M3.N17 (VBAT), M8.V2 (VBAT)
/VBUS: J1.1 (VBUS), M3.N29 (VBUS)
/VIGN: M3.S7 (VIGN), M8.V5 (VIGN)
/VREF2: M4.S13 (VREF2), M5.W2 (VREF)
/VR_ANALOG: M3.S8 (IN_DIG4), M11.E2 (OUT_A)
/VSS: M3.S14 (IN_AN_DIG3), M4.N20 (VSS)
/VVT1_1: M3.E10 (OUT_IO10), M6.W27 (LOW9), M6.W36 (LOW12)
/VVT1_2: M3.E21 (OUT_IO7), M6.W26 (LOW10), M6.W29 (LOW2)
/VVT2_B1: M3.E17 (OUT_PWM5), M6.W30 (SOLENOID_B2)
/VVT2_B2: M3.E16 (OUT_PWM4), M6.W31 (SOLENOID_B1)
/WASTEGATE: M3.E12 (OUT_IO2), M6.W34 (LOW4_DUAL)
GND: BT1.2 (-), C1.1, C2.1, C5.1, C6.1, C7.1, C8.1, C9.1, C10.1, C11.1, C12.1, C13.1, C14.1, C15.1, C16.1, C18.1, C19.1, G3.4, G3.5, G3.9, G3.10, G3.14, G3.15, J5.1, J6.1, J8.3, J10.S, M1.E1 (GND), M2.G (GND), M3.S2 (GND), M4.E1 (GND), M5.E2 (GND), M6.G (GND), M6.S3 (GND), M7.G (GND), M8.S1 (GND), M9.E6 (LSU_H-), M9.G (GND), M10.E1 (GND), M11.G (GND), P1.1, P1.2, P1.32, P1.59, R16.2, R17.2, R20.2, R21.2, R22.2, R23.2, S2.2, U1.1 (GND@1), U1.8 (SENSEA), U1.10 (GND@2), U1.11 (GND@3), U1.13 (SENSEB), U1.20 (GND@4), U1.SLUG1 (SLUG@1), U1.SLUG2 (SLUG@2), U1.SLUG3 (SLUG@3), U2.3 (GND), U2.5 (SA0/MISO), U2.8 (GND), U2.9 (GND), U3.4 (V-), U3.5 (+), U4.3 (GND), U4.9 (GND), U5.3 (GND), U5.9 (GND)
GNDA: M3.S32 (GNDA), M4.J2 (PULL_GNDA), M4.J3 (PULL_RES2), M4.J4 (PULL_O2S2), M4.J6 (PULL_RES1), M4.J8 (PULL_AUX3), M4.J11 (PULL_RES3), M4.J12 (PULL_MAP3), M4.J13 (PULL_MAP2), M4.J14 (PULL_MAP1), M4.J22 (PULL_KNOCK), M4.J23 (PULL_SENS4), M4.J24 (PULL_SENS3), M4.J25 (PULL_SENS2), M4.J26 (PULL_SENS1), M4.N2 (GNDA), P1.27, P1.33, P1.36, P1.50, P1.91, P1.99, P1.108
unnamed: BT1.1 (+), D9.2 (A)
unnamed: C3.1, D2.1 (K), U1.17 (VBOOT)
unnamed: C4.1, U1.4 (VCP)
unnamed: C4.2, R1.2
unnamed: C5.2, R5.2, U1.5 (ENA), U1.16 (ENB)
unnamed: C17.1, J10.T
unnamed: C17.2, U3.1, U3.2 (-)
unnamed: D1.1 (K), D2.2 (A), R1.1
unnamed: D3.2 (A), D4.2 (K), R16.1
unnamed: D5.2 (A), D8.2 (K), R17.1
unnamed: D6.2 (K), R20.1
unnamed: D7.2 (K), R21.1
unnamed: F1.1, P1.3, R9.1
unnamed: F2.1, P1.121
unnamed: G1.1, G1.6, G1.11
unnamed: G1.5, G1.10, G1.15
unnamed: G1.2, G1.7, G1.12
unnamed: G1.3, G1.8, G1.13
unnamed: G1.4, G1.9, G1.14
unnamed: G2.1, G2.6, G2.11
unnamed: G2.5, G2.10, G2.15
unnamed: G2.2, G2.7, G2.12
unnamed: G2.3, G2.8, G2.13
unnamed: G2.4, G2.9, G2.14
unnamed: G5.1, G5.6, G5.11
unnamed: G5.5, G5.10, G5.15
unnamed: G5.2, G5.7, G5.12
unnamed: G5.3, G5.8, G5.13
unnamed: G5.4, G5.9, G5.14
unnamed: J1.5 (GND), J1.6 (Shield), R23.1
unnamed: J8.1, M9.W8 (V33_OUT)
unnamed: J8.2, M9.W7 (SWCLK)
unnamed: J8.4, M9.W6 (SWDIO)
unnamed: J8.5, M9.W5 (nReset)
unnamed: M9.J2 (SEL2), M9.J_VCC2 (PULL_UP2)
unnamed: M9.W2 (CAN_VIO), M10.V2 (CAN_VIO)
unnamed: M9.W4 (CAN_TX), M10.V5 (CAN_TX)
unnamed: M9.W3 (CAN_RX), M10.V6 (CAN_RX)
unnamed: P1.9, P9.1
unnamed: P1.10, P10.1
unnamed: P1.11, P11.1
unnamed: P1.12, P12.1
unnamed: P1.13, P13.1
unnamed: P1.17, P17.1
unnamed: P1.20, P20.1
unnamed: P1.21, R2.1, R8.2
unnamed: P1.23, R3.2
unnamed: P1.28, P28.1
unnamed: P1.37, R4.1
unnamed: P1.40, P40.1
unnamed: P1.41, P41.1
unnamed: P1.43, P43.1
unnamed: P1.44, P44.1
unnamed: P1.45, P45.1
unnamed: P1.46, P46.1
unnamed: P1.48, P48.1
unnamed: P1.49, P49.1
unnamed: P1.51, R10.1
unnamed: P1.52, R11.1
unnamed: P1.56, P56.1
unnamed: P1.61, P61.1
unnamed: P1.63, P63.1
unnamed: P1.64, P64.1
unnamed: P1.66, P66.1
unnamed: P1.67, P67.1
unnamed: P1.68, P68.1
unnamed: P1.69, P69.1
unnamed: P1.70, R12.1
unnamed: P1.71, R13.1
unnamed: P1.74, P74.1
unnamed: P1.80, P80.1
unnamed: M6.S8 (OUT_LOW1), P6.1
unnamed: M6.W9 (OUT_LOW7_PULLUP), P7.1
unnamed: M6.S12 (OUT_LOW8_PULLUP), P8.1
unnamed: M3.N19 (I2C_SCL), R18.2, U2.2 (SCL/SCLK)
unnamed: M3.N18 (I2C_SDA), R19.2, U2.4 (SDA/MOSI)
unnamed: U3.6 (-), U3.7

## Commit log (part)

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2025-11-24 Modify BOARD_PREFIX and BOARD_SUFFIX in revision.txt
    Updated BOARD_PREFIX and cleared BOARD_SUFFIX.
2025-11-24 Añadiendo PCB greenenergy_ecu y configurando revision.txt
2025-11-24 pisgtaintercalada
2025-11-24 errorcon subfijo solucionado
2025-11-24 version 8
2025-11-27 [skip actions] Auto-generated board v2.1
2025-11-28 ghgh
2025-12-20 wewe
2025-12-21 Update GreenEnergy ECU frame (KiCad PCB)
2026-01-13 tilo
2026-01-13 Ignore gerber outputs
2026-01-16 casi
2026-01-16 hola
2026-01-17 holi
2026-01-26 weew
2026-01-26 weweaawqawa
2026-01-26 holu
